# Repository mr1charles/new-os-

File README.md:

# HelixOS

A macOS-style operating system for everyday laptops, starting with an HP 14" / Pavilion x360
(11th-gen Intel). HelixOS is a Linux distribution with its own desktop built from scratch:

- **Dynamic Island.** A notch that hangs from the menu bar and morphs to show what's
  happening: notifications (with their buttons), music, volume and brightness, charging,
  timers, and apps' live activities like file copies and long Terminal commands.
- **A built-in assistant.** It uses Claude in the cloud when you're online and have a key.
  Otherwise it runs a model on the laptop through Ollama. It can change settings, open apps,
  find files, write notes, set timers, and remember things about you.
- **Dual Space.** One password field at login: each password (or fingerprint or face) opens its
  own private space with separate apps, files, and settings.
- **A familiar desktop, your way.** Menu bar, Dock or a Windows-style taskbar, Spotlight and
  Launchpad, Control Center, Notification Center, desktop widgets (weather, batteries, clock,
  calendar), Liquid Glass (clear or tinted), and icon styles. Snap windows into halves and
  quarters, let the desktop auto-arrange them, or tile. Ask the assistant to "make it look
  more like Windows" and it restyles everything live.
- **Opens anything.** Windows `.exe`/`.msi` (Wine), Flathub links and Flatpaks, AppImages, Arch
  packages, and Android `.apk` (Waydroid), asking first and showing progress in the island.
- **Apps with intelligence built in.** Settings, Files, Notes, Terminal, Mail (Gmail and
  iCloud), Messages (text without a phone), Calendar, and an App Store.

> **Status:** early development. Milestones 0–2 are done: the monorepo, design system,
> desktop shell, and assistant daemon. The bootable ISO arrives in milestone 8.
> See [docs/ROADMAP.md](docs/ROADMAP.md).

## How it's built

HelixOS reuses the Linux kernel, drivers, and the Hyprland Wayland compositor. Everything you
see and touch is built in this repo.

| Layer | Technology | Where |
|---|---|---|
| Apps | Tauri 2 + React + TypeScript | [`apps/`](apps): Settings, Files, Notes, Terminal, Calculator |
| App UI kit and SDK | React components; typed IPC, settings, assistant | [`packages/ui/`](packages/ui), [`packages/sdk/`](packages/sdk) |
| Desktop shell | AGS/Astal (TypeScript, GTK4, layer-shell) | [`shell/`](shell) |
| Assistant | Rust daemon, Claude API + Ollama | [`services/assistantd/`](services/assistantd) |
| System integration | Rust libraries | [`services/syslib/`](services/syslib), [`services/appkit/`](services/appkit) |
| Design system | tokens → GTK CSS + web CSS | [`packages/design-tokens/`](packages/design-tokens) |
| Base | Arch Linux, linux-zen, Hyprland, greetd | `distro/` (milestone 8) |

The full picture is in [docs/ARCHITECTURE.md](docs/ARCHITECTURE.md).

## Try it

You need an Arch-based Linux machine (or VM) for the desktop. The checks run anywhere with
Node 22 and Rust (plus WebKitGTK 4.1 for the app backends):

```bash
pnpm install
pnpm check             # design tokens, typecheck, lint, format, 181 unit tests
cargo test --workspace # daemon, system libraries, app backends: 137 tests
```

The Settings app's interface also runs in any browser against sample data:

```bash
pnpm --filter @helixos/settings dev   # then open http://localhost:1420
```

To try the whole OS on a Linux machine without installing anything, use testing mode: a
rootless container with everything HelixOS needs, using your real Wi-Fi, sound, and Bluetooth
([details](docs/DEVELOPING.md#testing-mode-the-whole-os-in-a-container)):

```bash
scripts/install-preview.sh   # adds "HelixOS Preview" to your app menu: set up, start, update
scripts/live.sh run          # or from a terminal: HelixOS in a window (full screen from a console)
```

## Docs

- [Architecture](docs/ARCHITECTURE.md): layers, processes, files, and security model
- [Roadmap](docs/ROADMAP.md): milestones and what's done
- [Developing](docs/DEVELOPING.md): setup, running the shell, tests
- [Assistant](docs/ASSISTANT.md): setup, privacy, tools, and the local API
- [Hardware](docs/HARDWARE.md): the HP laptop, drivers, and a checklist to run on it

## License

MIT. Wallpapers and icons in `shell/assets` are original artwork under the same license.
HelixOS is an independent project, not affiliated with Apple or HP.

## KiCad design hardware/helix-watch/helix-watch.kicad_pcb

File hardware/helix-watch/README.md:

# Helix Watch — main board (rev A, placement stage)

A 44 mm round, 4-layer, 0.8 mm board for a 1.75" round AMOLED smartwatch built around an
ESP32-S3 module. `build.py` generates `helix-watch.kicad_pcb` (open it in KiCad 9/10).

## Where it actually stands

| Done | Not done |
|---|---|
| Parts chosen, placed on both sides, 44 mm outline, antenna keepout | **Routing** — nets are assigned (ratsnest), no copper traces yet |
| Net-assigned: power, I²C, display bus, button, haptics, charger, battery sense, USB | No schematic yet (the netlist lives in `build.py`) |
| DRC clean apart from "not routed" | **Gerbers deliberately not exported** — an unrouted board would fab as a blank |

It is a solid starting point for an engineer (or you, in KiCad), **not something to send to a fab today**.
See "Before you order".

## What the hardware can and can't do

The board gives you the *capability*; the features you listed are mostly **software** on top of it.

| You asked for | Reality on this board |
|---|---|
| Control your phone | BLE 5 to the phone. Needs a companion app (Android / iOS). |
| Text via WhatsApp / Telegram / Google Messages | Possible on **Android**: the companion app forwards notifications and fires their reply actions. |
| iMessage | **Not possible** from a third-party watch. iOS shows notifications over ANCS (read-only), but only Apple Watch can reply to iMessage. |
| Watch YouTube / TikTok | Not natively — those apps can't run on a microcontroller. Practical route: phone/PC companion fetches + transcodes to MJPEG, streams over Wi-Fi/BLE to the 466×466 panel (low fps, no DRM content, ToS caveats). A real app-processor watch (Qualcomm W5, Ambiq Apollo4+Wi-Fi) is a different, much bigger board. |
| Sleep hours, calories, steps | Yes (consumer-grade): IMU (BMI270) + PPG heart-rate/SpO₂ flex (MAX30102) → steps, sleep stages from motion + HR, calories from HR + motion + profile. |
| "Predict if something bad happens" | Fall detection (IMU) and abnormal-HR alerts are realistic. Real *prediction* of illness isn't — and this isn't a medical device; don't market it as one. |
| App store | A store of signed, sandboxed apps (e.g. WASM or Lua) running on the ESP32-S3 with a watch API. A software project on top of the board; could be built into HelixOS. |

## Architecture

```
            ┌────────────── ESP32-S3-WROOM-1-N16R8 (Wi-Fi + BLE, 16 MB flash, 8 MB PSRAM) ──────────────┐
 BLE/Wi-Fi ─┤ QSPI ─► 1.75" 466×466 AMOLED (FPC J1, touch on panel flex, I²C)                           │
            │ I²C  ─► BMI270 IMU · PPG flex J3 (MAX30102 on a small flex under the case back)            │
            │ GPIO ─► side button · haptic motor (SI2302 + flyback diode) · battery-voltage ADC          │
            │ USB  ─► programming pads J4 (native USB, no USB chip needed)                               │
            └────────────────────────────────────────────────────────────────────────────────────────────┘
 Charge contacts P1 ─► MCP73831 (200 mA) ─► 1S LiPo (J2) ─► AP2112K-3.3 (system) ─► AP2112K-1.8 (PPG core)
```

Front (display side): module, display FPC, IMU, charger, regulators, battery connector, button, haptic driver.
Back (skin side): charge contacts, PPG flex pads, programming pads, motor pads.

## GPIO map (ESP32-S3)

| Net | GPIO | | Net | GPIO |
|---|---|---|---|---|
| VBAT_SENSE | IO1 (ADC) | | DISP_D0–D3 | IO11–IO14 |
| BTN | IO2 | | DISP_RST | IO15 |
| IMU_INT | IO4 | | TOUCH_INT / RST | IO16 / IO17 |
| SDA / SCL | IO5 / IO6 | | DISP_TE | IO18 |
| MOTOR_DRV | IO7 | | USB D− / D+ | IO19 / IO20 |
| CHG_STAT | IO8 | | I2S BCLK/WS/DOUT (audio rev) | IO21 / IO47 / IO48 |
| DISP_CS / CLK | IO9 / IO10 | | PPG_INT | IO42 |
| BOOT | IO0 | | UART log | IO44 / IO43 |

IO35–37 are left alone (octal PSRAM). IO3/45/46 are left alone (strapping).

## Before you order (don't skip)

1. **Verify every pin against the datasheets.** ESP32 pad numbers are from the datasheet; I'm confident
   about the regulators/FET/diode, but check the **BMI270** pin mapping and the **display FPC pinout**
   (`J1` has no nets: pinouts differ per panel — pick the panel first, then wire it).
2. **Pick the panel and the PPG part, then re-check the stack-up.** Battery, display and case back all
   compete for the same 44 mm; PPG needs optical access through the case back, so it sits on a flex, not
   on this board.
3. **Route it.** 4-layer: In1 = GND plane, In2 = power. Keep the antenna keepout empty and the battery
   and any metal away from the module's antenna end.
4. **Battery safety.** MCP73831 has no cell protection — use a LiPo with a built-in protection circuit
   and add a fuel gauge (MAX17048) if you want an accurate %. Don't charge unprotected cells.
5. **Power.** AP2112K linear regulators are simple but wasteful; a buck (e.g. TPS62743) would roughly
   double idle battery life. Video streaming will drain 400 mAh in a couple of hours regardless.
6. **Audio** (speaker/mic) isn't populated — I2S pins are reserved for a later revision.
7. Selling a radio device needs FCC/CE (and a certified module like this one helps), plus battery
   shipping rules (UN38.3).

## Regenerating

```bash
python3 hardware/helix-watch/build.py     # rewrites helix-watch.kicad_pcb
kicad-cli pcb drc hardware/helix-watch/helix-watch.kicad_pcb
```

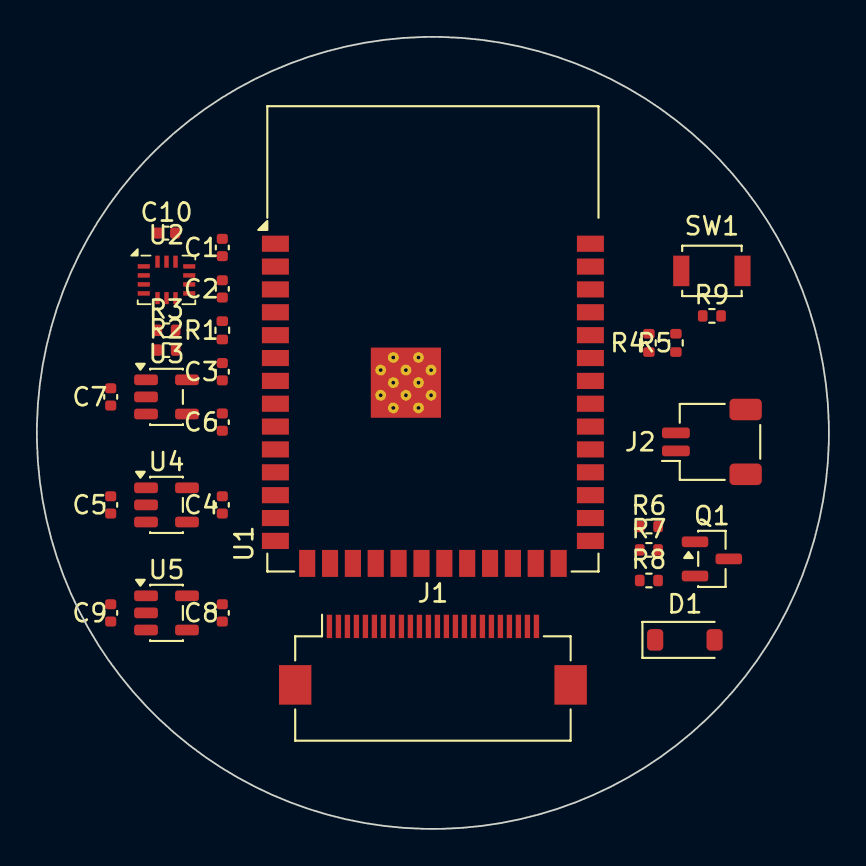
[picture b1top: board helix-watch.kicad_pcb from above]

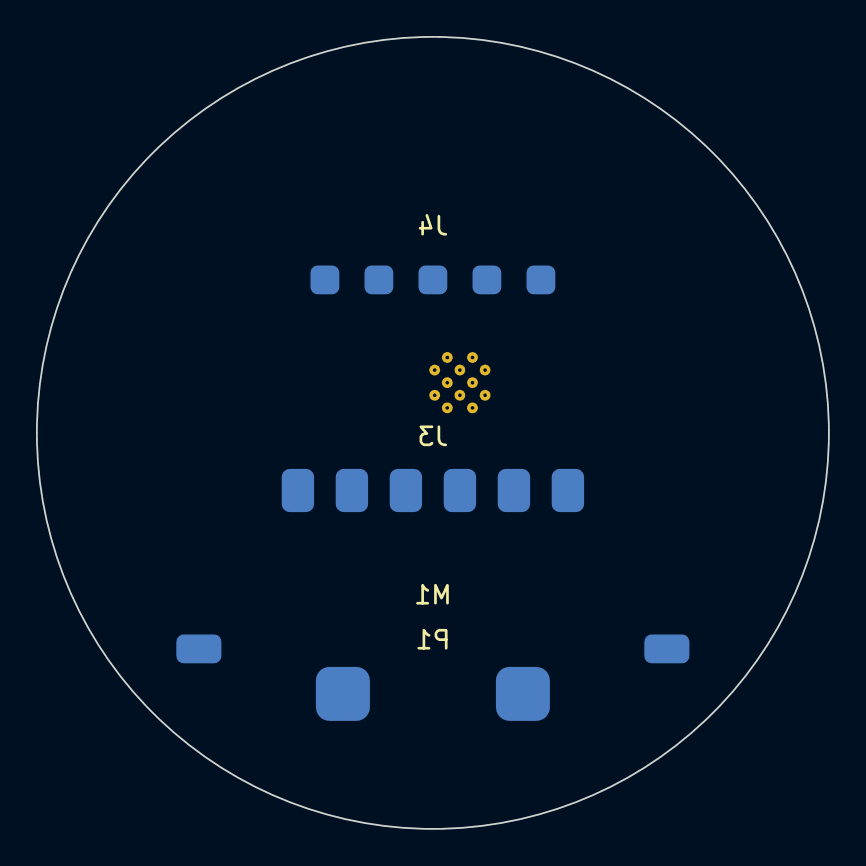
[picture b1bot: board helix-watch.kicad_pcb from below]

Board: 4 copper layers, 44.0 x 44.0 mm, 33 parts (4 on the bottom side), 19 nets, no tracks yet.

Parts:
C1: 10uF; C_0402_1005Metric
C2, C10: 100nF; C_0402_1005Metric
C3, C4, C5, C8, C9: 1uF; C_0402_1005Metric
C6, C7: 4.7uF; C_0402_1005Metric
D1: 1N4148W; D_SOD-123
J1: Display FPC 24p 0.5mm; Hirose_FH12-24S-0.5SH_1x24-1MP_P0.50mm_Horizontal
J2: LiPo 400mAh; JST_SH_SM02B-SRSS-TB_1x02-1MP_P1.00mm_Horizontal
J3: PPG sensor flex (6 pads)
J4: Programming pads
M1: ERM motor
P1: Charge contacts
Q1: SI2302; SOT-23
R1, R3, R9: 10k; R_0402_1005Metric
R2: 5k; R_0402_1005Metric
R4, R5: 4.7k; R_0402_1005Metric
R6, R7, R8: 100k; R_0402_1005Metric
SW1: Side button; SW_SPST_B3U-1000P
U1: ESP32-S3-WROOM-1-N16R8; ESP32-S3-WROOM-1
U2: BMI270; Bosch_LGA-14_3x2.5mm_P0.5mm
U3: MCP73831T-2ACI/OT; SOT-23-5
U4: AP2112K-3.3; SOT-23-5
U5: AP2112K-1.8; SOT-23-5

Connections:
+1V8: C9.1, J3.2, U5.5
+3V3: C1.1, C2.1, C5.1, C8.1, C10.1, D1.1, J3.1, M1.1, R1.2, R3.2, R4.2, R5.2, R9.2, U1.2, U2.5, U2.8, U2.12, U4.5, U5.1, U5.3
BOOT: J4.3, U1.27
BTN: R9.1, SW1.1, U1.38
CHG_PROG: R2.1, U3.5
CHG_STAT_OD: R3.1, U3.1
EN: C3.1, J4.4, R1.1, U1.3
GND: C1.2, C2.2, C3.2, C4.2, C5.2, C6.2, C7.2, C8.2, C9.2, C10.2, J2.2, J3.6, J4.5, P1.2, Q1.2, R2.2, R7.2, R8.2, SW1.2, U1.1, U1.40, U1.41, U2.1, U2.6, U2.7, U3.2, U4.2, U5.2
IMU_INT: U1.4, U2.4
MOTOR_DRV: Q1.1, R8.1, U1.7
MOTOR_N: D1.2, M1.2, Q1.3
PPG_INT: J3.5, U1.35
SCL: J3.4, R5.1, U1.6, U2.13
SDA: J3.3, R4.1, U1.5, U2.14
USB_DN: J4.2, U1.13
USB_DP: J4.1, U1.14
VBAT: C4.1, C7.1, J2.1, R6.1, U3.3, U4.1, U4.3
VBAT_SENSE: R6.2, R7.1, U1.39
VBUS: C6.1, P1.1, U3.4

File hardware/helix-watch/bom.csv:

Qty,Value,Footprint,Refs
1,10uF,C_0402_1005Metric,C1
2,100nF,C_0402_1005Metric,C2 C10
5,1uF,C_0402_1005Metric,C3 C4 C5 C8 C9
2,4.7uF,C_0402_1005Metric,C6 C7
1,1N4148W,D_SOD-123,D1
1,Display FPC 24p 0.5mm,Hirose_FH12-24S-0.5SH_1x24-1MP_P0.50mm_Horizontal,J1
1,LiPo 400mAh,JST_SH_SM02B-SRSS-TB_1x02-1MP_P1.00mm_Horizontal,J2
1,PPG sensor flex (6 pads),pads on PCB,J3
1,Programming pads,pads on PCB,J4
1,ERM motor,pads on PCB,M1
1,Charge contacts,pads on PCB,P1
1,SI2302,SOT-23,Q1
3,10k,R_0402_1005Metric,R1 R3 R9
1,5k,R_0402_1005Metric,R2
2,4.7k,R_0402_1005Metric,R4 R5
3,100k,R_0402_1005Metric,R6 R7 R8
1,Side button,SW_SPST_B3U-1000P,SW1
1,ESP32-S3-WROOM-1-N16R8,ESP32-S3-WROOM-1,U1
1,BMI270,Bosch_LGA-14_3x2.5mm_P0.5mm,U2
1,MCP73831T-2ACI/OT,SOT-23-5,U3
1,AP2112K-3.3,SOT-23-5,U4
1,AP2112K-1.8,SOT-23-5,U5
